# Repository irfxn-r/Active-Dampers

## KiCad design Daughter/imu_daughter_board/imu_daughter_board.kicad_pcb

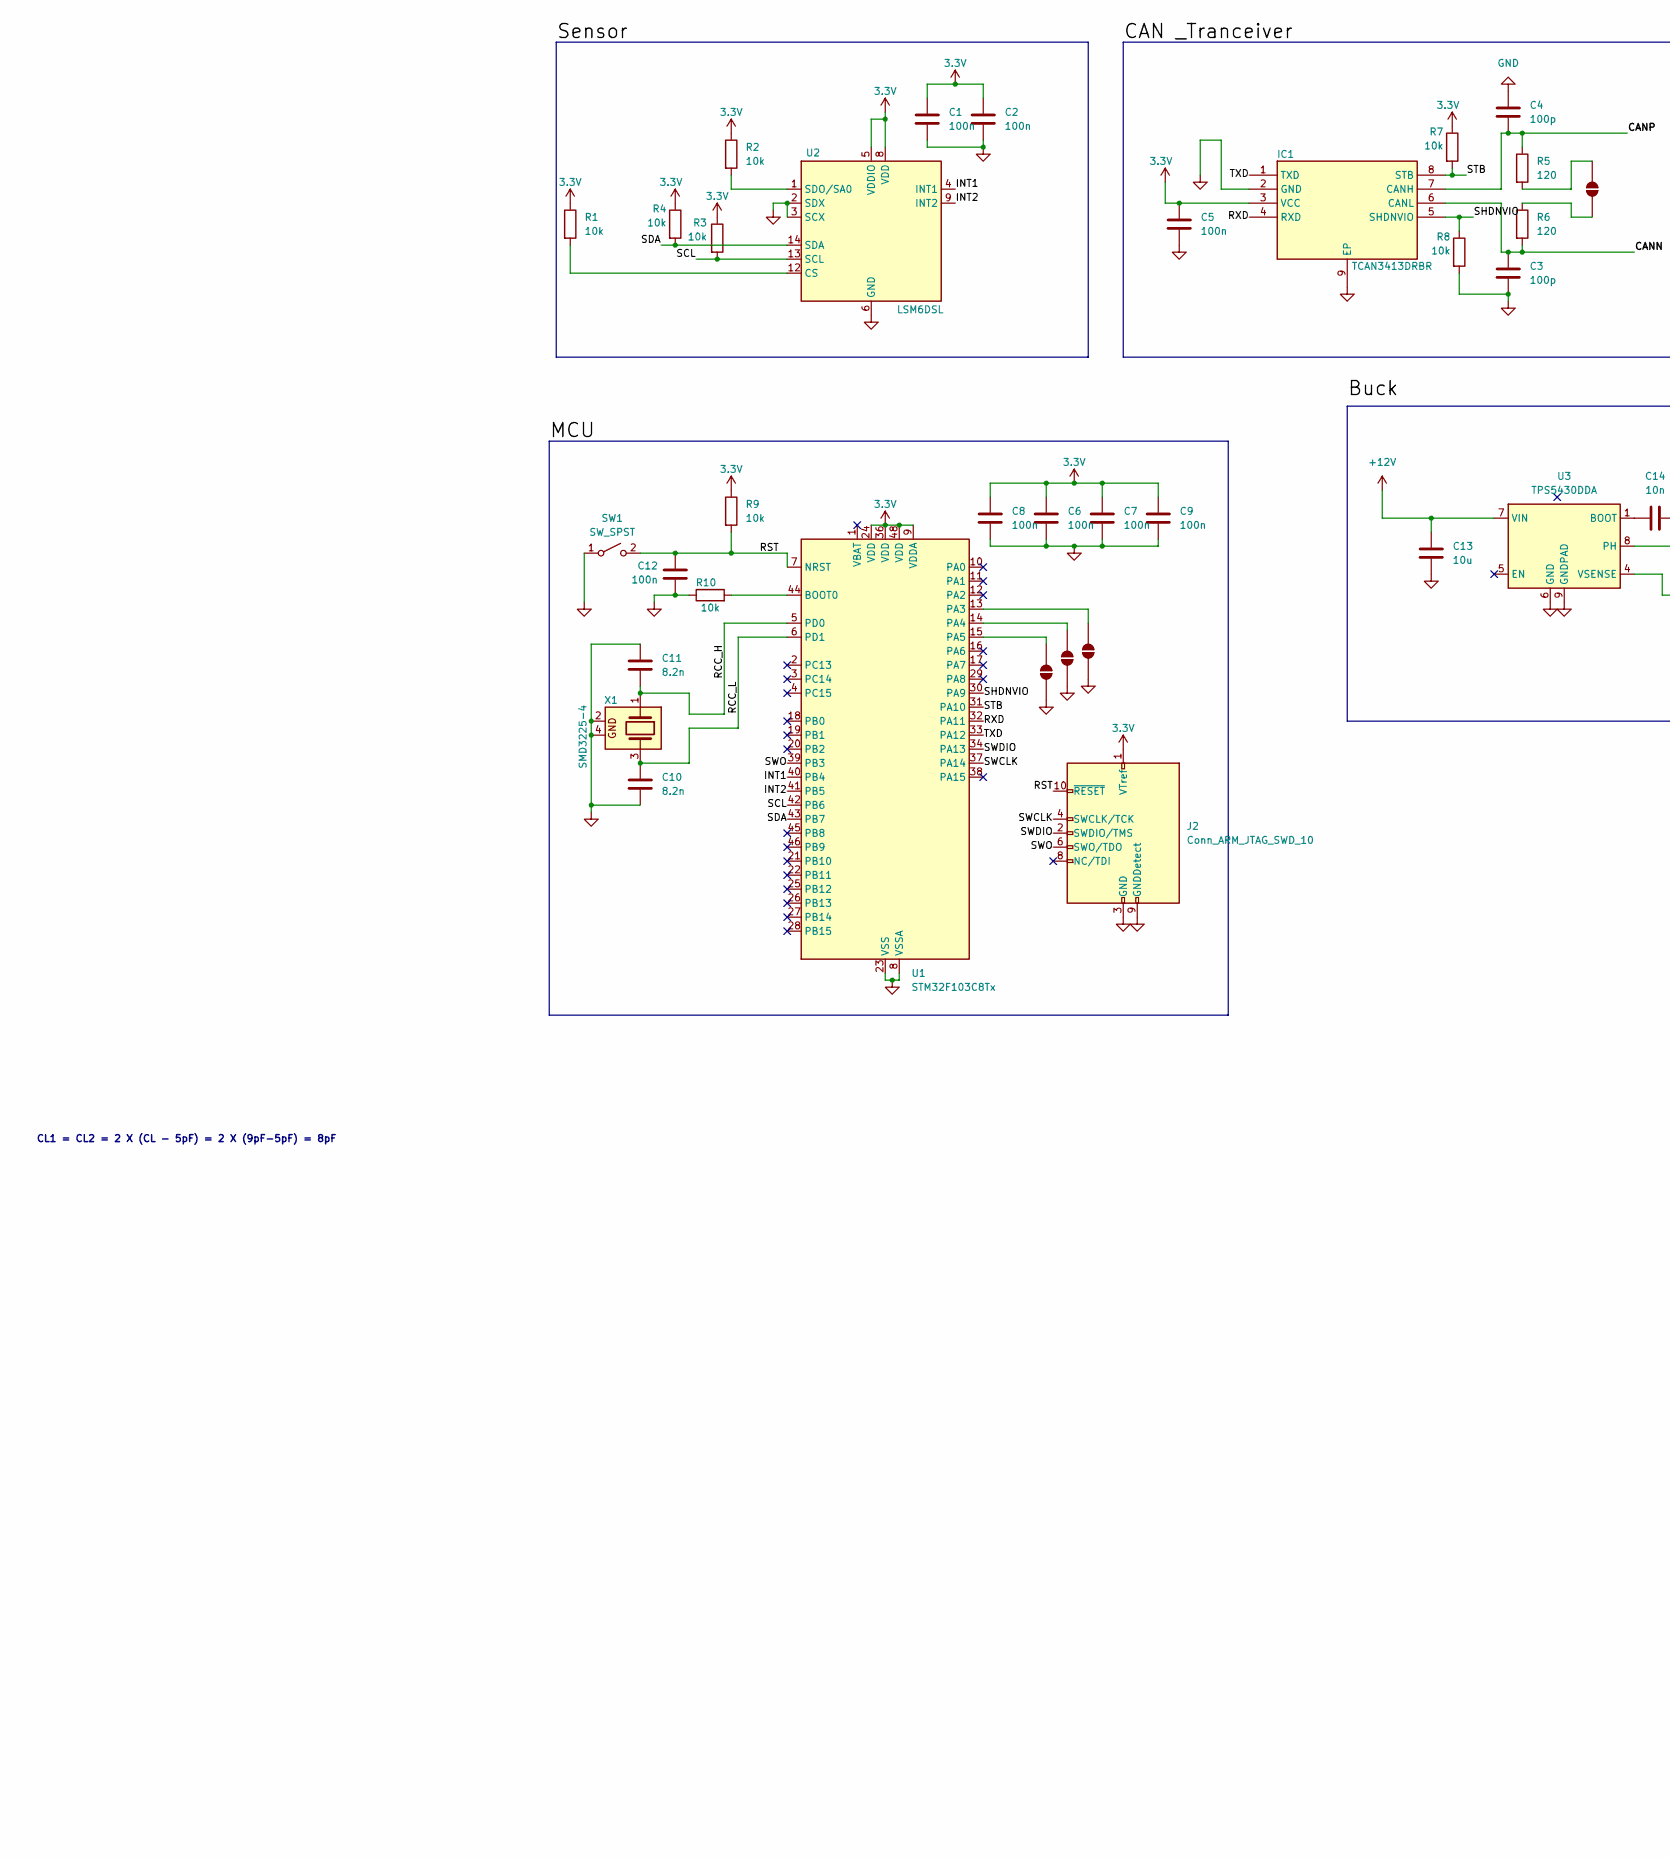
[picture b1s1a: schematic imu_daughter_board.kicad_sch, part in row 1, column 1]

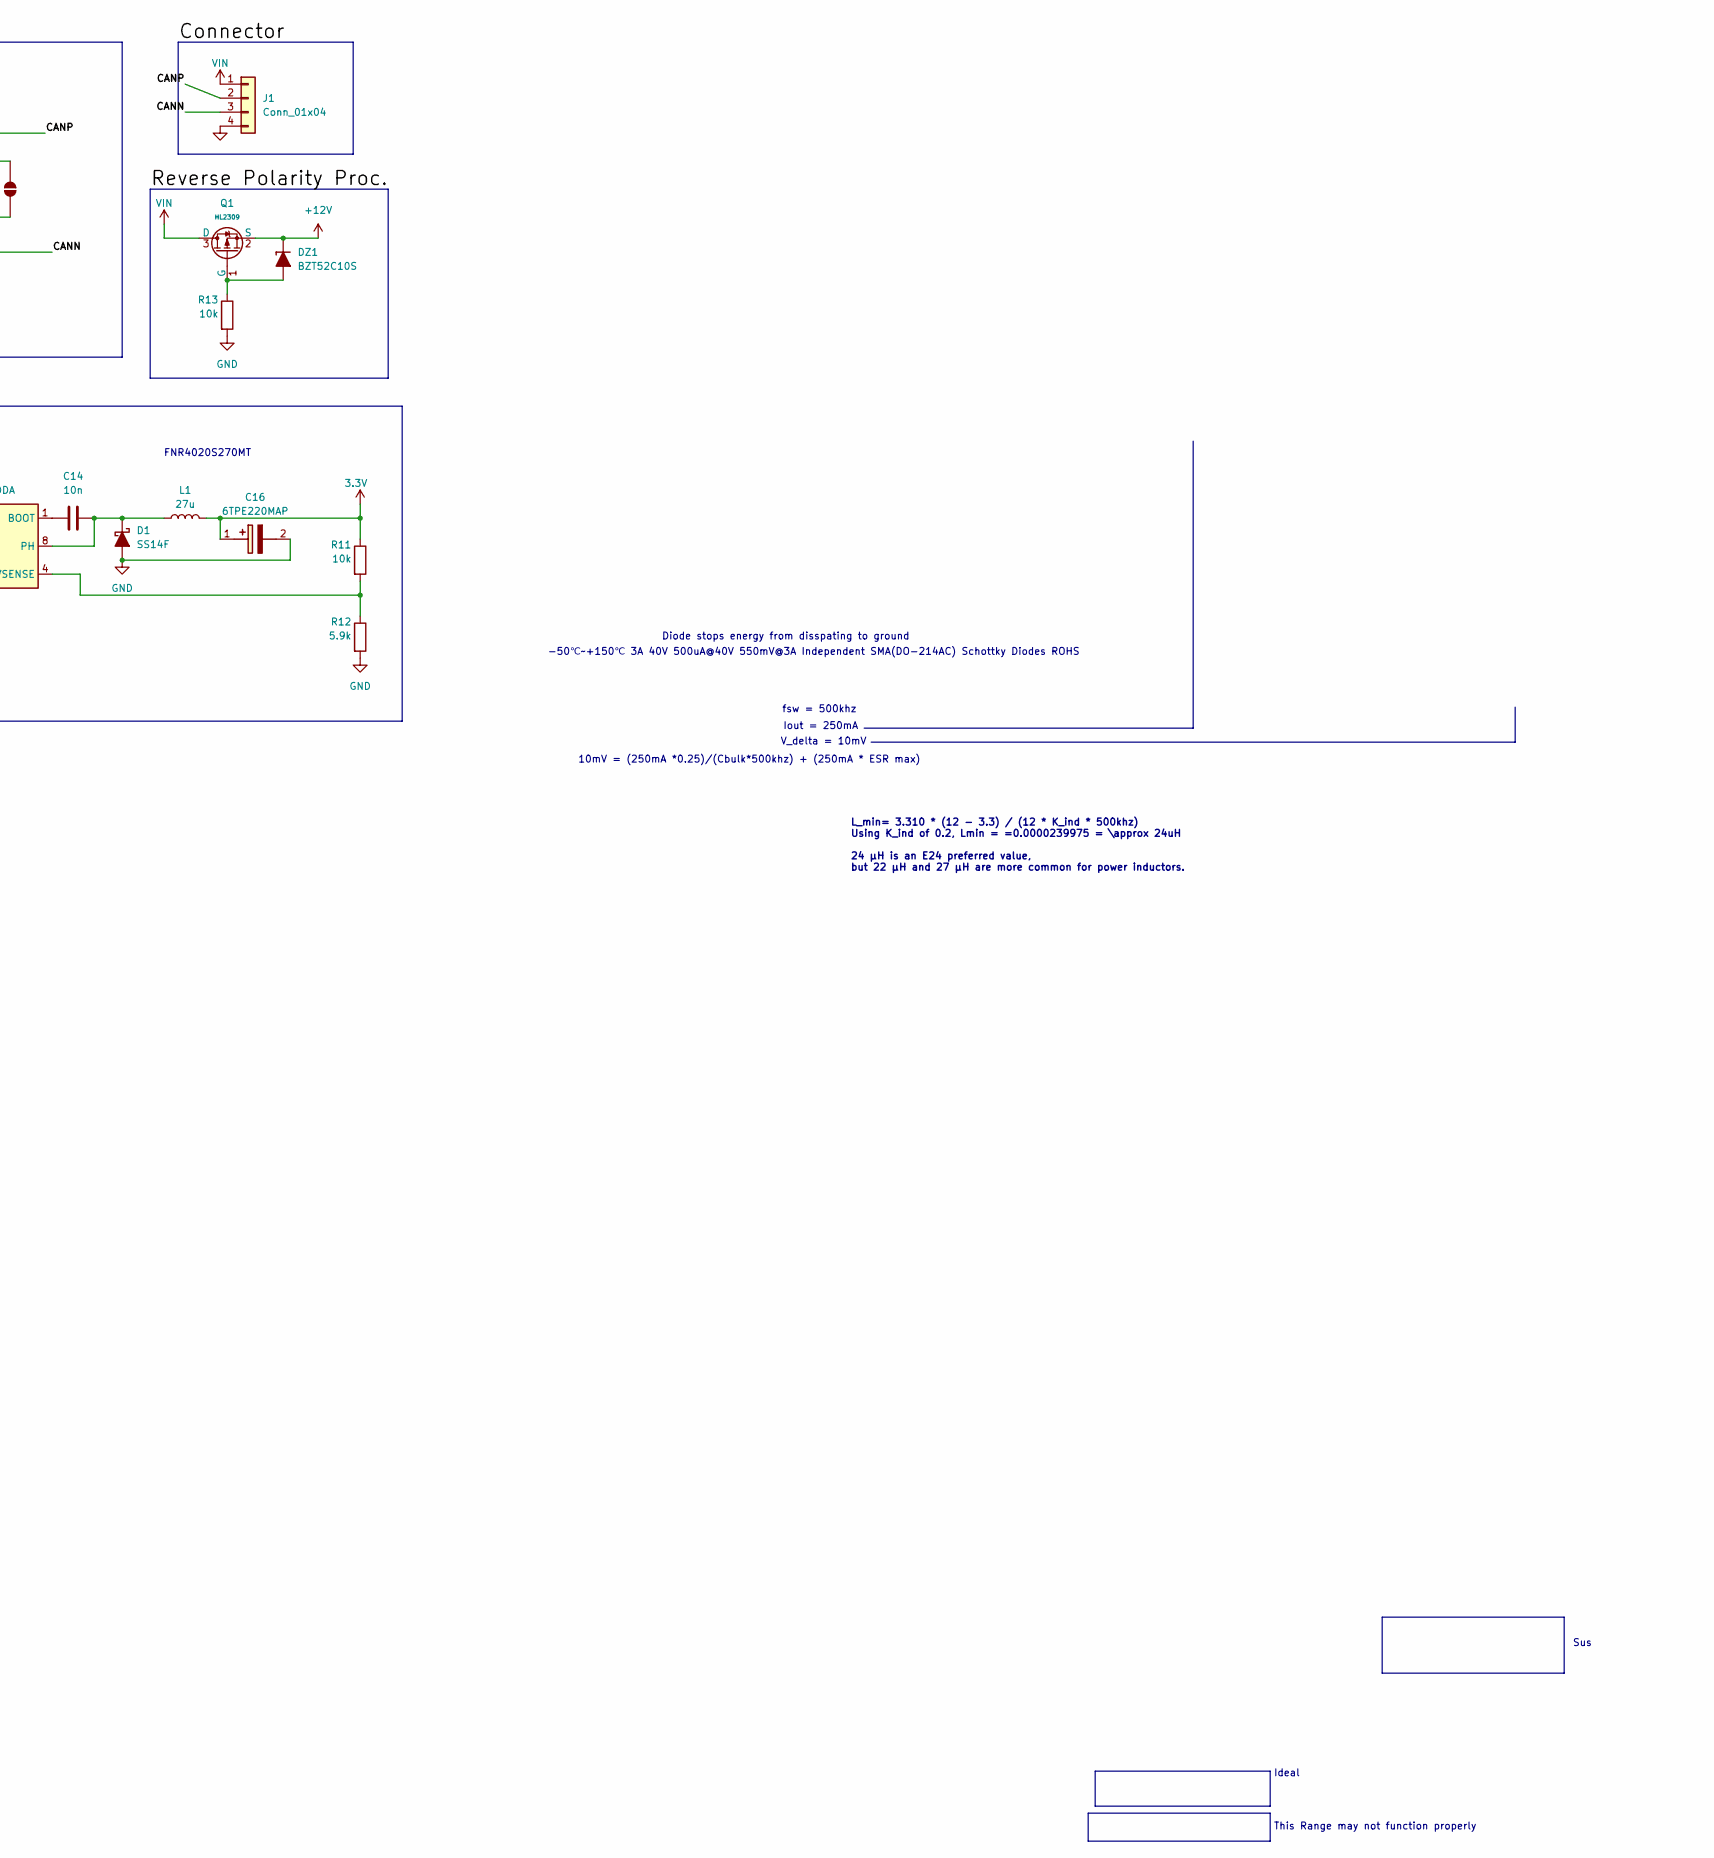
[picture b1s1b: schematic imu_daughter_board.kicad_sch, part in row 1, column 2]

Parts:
C1, C2, C5, C6, C7, C8, C9, C12: 100n; C_0402_1005Metric
C3, C4: 100p; C_0402_1005Metric
C10, C11: 8.2n; C_0402_1005Metric
C13: 10u; C_0603_1608Metric_Pad1.05x0.95mm
C14: 10n; C_0603_1608Metric_Pad1.05x0.95mm
C16: 6TPE220MAP; 2R5TAE330MF; Mouser Part Number 667-6TPE220MAP
D1: SS14F; D_SMAFL
DZ1: BZT52C10S; D_SOD-323
IC1: TCAN3413DRBR; SON65P300X300X100-9N-D; Mouser Part Number 595-TCAN3413DRBR
J1: Conn_01x04; SolderWire-0.5sqmm_1x04_P4.6mm_D0.9mm_OD2.1mm
J2: Conn_ARM_JTAG_SWD_10; SHF10501FDTH
JP1, JP2, JP3, JP4: SolderJumper_2_Open; SolderJumper-2_P1.3mm_Open_Pad1.0x1.5mm
L1: 27u; L_Taiyo-Yuden_MD-4040
Q1: HL2309; Q_SOT-23; Part HL2309; LCSC C28646263
R1, R2, R3, R4, R7, R8, R9, R10: 10k; C_0402_1005Metric
R5, R6: 120; R_0402_1005Metric
R11, R13: 10k; R_0603_1608Metric
R12: 5.9k; R_0603_1608Metric
SW1: SW_SPST; SW_SPST_TS-1088-xR025
U1: STM32F103C8Tx; LQFP-48_7x7mm_P0.5mm
U2: LSM6DSL; LGA-14_3x2.5mm_P0.5mm_LayoutBorder3x4y
U3: TPS5430DDA; TI_SO-PowerPAD-8_ThermalVias
X1: SMD3225-4; Crystal_SMD_3225-4Pin_3.2x2.5mm

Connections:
3.3V: C1.2, C2.1, C5.2, C6.2, C7.1, C8.2, C9.1, C16.1 (+), IC1.3 (VCC), J2.1 (VTref), L1.2, R1.1, R1.2, R2.1, R3.1, R4.1, R7.1, R9.1, R11.1, U1.9 (VDDA), U1.24 (VDD), U1.36 (VDD), U1.48 (VDD), U2.5 (VDDIO), U2.8 (VDD), U2.12 (CS)
+12V: C13.1, DZ1.1 (K), Q1.2 (S), U3.7 (VIN)
/CANN: C3.1, IC1.6 (CANL), J1.3, R6.2
/CANP: C4.2, IC1.7 (CANH), J1.2, R5.1
/INT1: U1.40 (PB4), U2.4 (INT1)
/INT2: U1.41 (PB5), U2.9 (INT2)
/RCC_H: C11.1, U1.5 (PD0), X1.1
/RCC_L: C10.2, U1.6 (PD1), X1.3
/RST: C12.2, J2.10 (~RESET), R9.2, SW1.2 (B), U1.7 (NRST)
/RXD: IC1.4 (RXD), U1.32 (PA11)
/SCL: R3.2, U1.42 (PB6), U2.13 (SCL)
/SDA: R4.2, U1.43 (PB7), U2.14 (SDA)
/SHDNVIO: IC1.5 (SHDNVIO), R8.1, U1.30 (PA9)
/STB: IC1.8 (STB), R7.2, U1.31 (PA10)
/SWCLK: J2.4 (SWCLK/TCK), U1.37 (PA14)
/SWDIO: J2.2 (SWDIO/TMS), U1.34 (PA13)
/SWO: J2.6 (SWO/TDO), U1.39 (PB3)
/TXD: IC1.1 (TXD), U1.33 (PA12)
GND: C1.1, C2.2, C3.2, C4.1, C5.1, C6.1, C7.2, C8.1, C9.2, C10.1, C11.2, C12.1, C13.2, C16.2 (-), D1.2 (A), IC1.2 (GND), IC1.9 (EP), J1.4, J2.3 (GND), J2.5 (GND), J2.9 (GNDDetect), JP2.1 (A), JP3.1 (A), JP4.1 (A), R8.2, R10.1, R12.2, R13.2, SW1.1 (A), U1.8 (VSSA), U1.23 (VSS), U1.35 (VSS), U1.47 (VSS), U2.2 (SDX), U2.3 (SCX), U2.6 (GND), U2.7 (GND), U3.6 (GND), U3.9 (GNDPAD), X1.2, X1.4
unnamed: C14.2, D1.1 (K), L1.1, U3.8 (PH)
unnamed: DZ1.2 (A), Q1.1 (G), R13.1
unnamed: JP1.1 (A), R6.1
unnamed: JP1.2 (B), R5.2
unnamed: JP2.2 (B), U1.15 (PA5)
unnamed: JP3.2 (B), U1.14 (PA4)
unnamed: JP4.2 (B), U1.13 (PA3)
unnamed: R10.2, U1.44 (BOOT0)
unnamed: R2.2, U2.1 (SDO/SA0)
unnamed: C14.1, U3.1 (BOOT)
unnamed: R11.2, R12.1, U3.4 (VSENSE)
VIN: J1.1, Q1.3 (D)

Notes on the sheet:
-50℃~+150℃ 3A 40V 500uA@40V 550mV@3A Independent SMA(DO-214AC) Schottky Diodes ROHS
This Range may not function properly
Sus
10mV = (250mA *0.25)/(Cbulk*500khz) + (250mA * ESR max)
CL1 = CL2 = 2 X (CL - 5pF) = 2 X (9pF-5pF) = 8pF
V_delta = 10mV
Ideal
Vpp max = 20mV
R2 = R1 * 1.221 / (3.3 - 1.221) R1 = 10kohm R2 = 10e3 * 1.221 / (3.3 - 1.221) 5873.01587302
Maybe not important yet
L_min= 3.310 * (12 - 3.3) / (12 * K_ind * 500khz) Using K_ind of 0.2, Lmin = =0.0000239975 = \approx 24uH 24 µH is an E24 preferred value, but 22 µH and 27 µH are more common for power inductors.
Use 5.90 kΩ, 1%-it's a standard E96 value closest to your calculated 5.873 kΩ.
fsw = 500khz
FNR4020S270MT
Diode stops energy from disspating to ground
Iout = 250mA

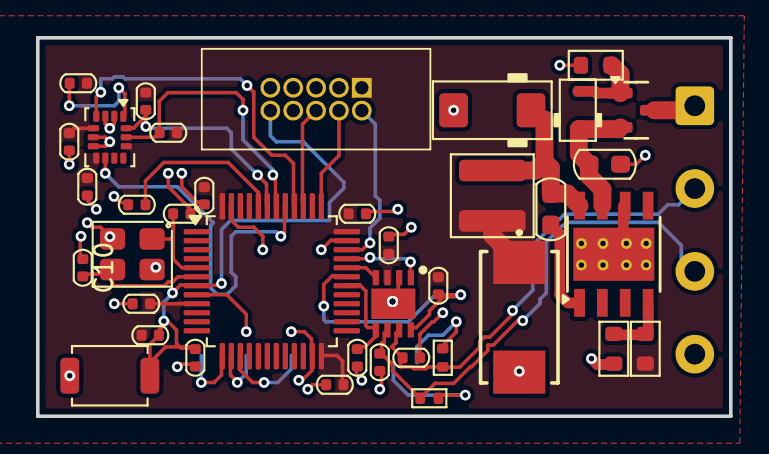
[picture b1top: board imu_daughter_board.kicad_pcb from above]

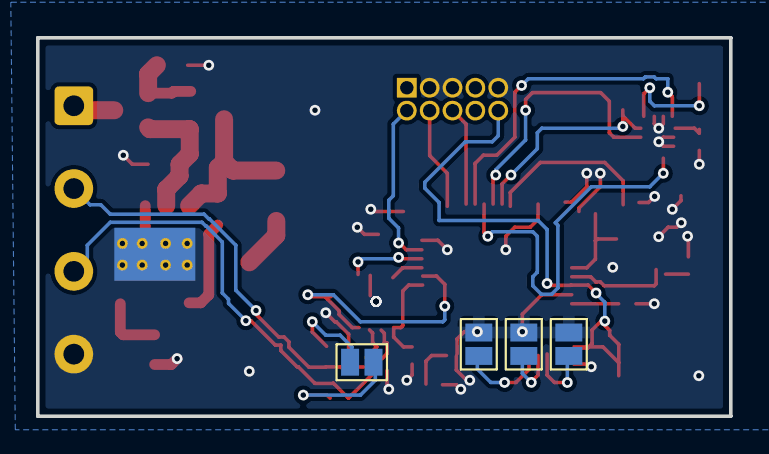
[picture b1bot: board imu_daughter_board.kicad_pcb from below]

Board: 2 copper layers, 38.5 x 21.0 mm, 43 parts (4 on the bottom side), 31 nets.

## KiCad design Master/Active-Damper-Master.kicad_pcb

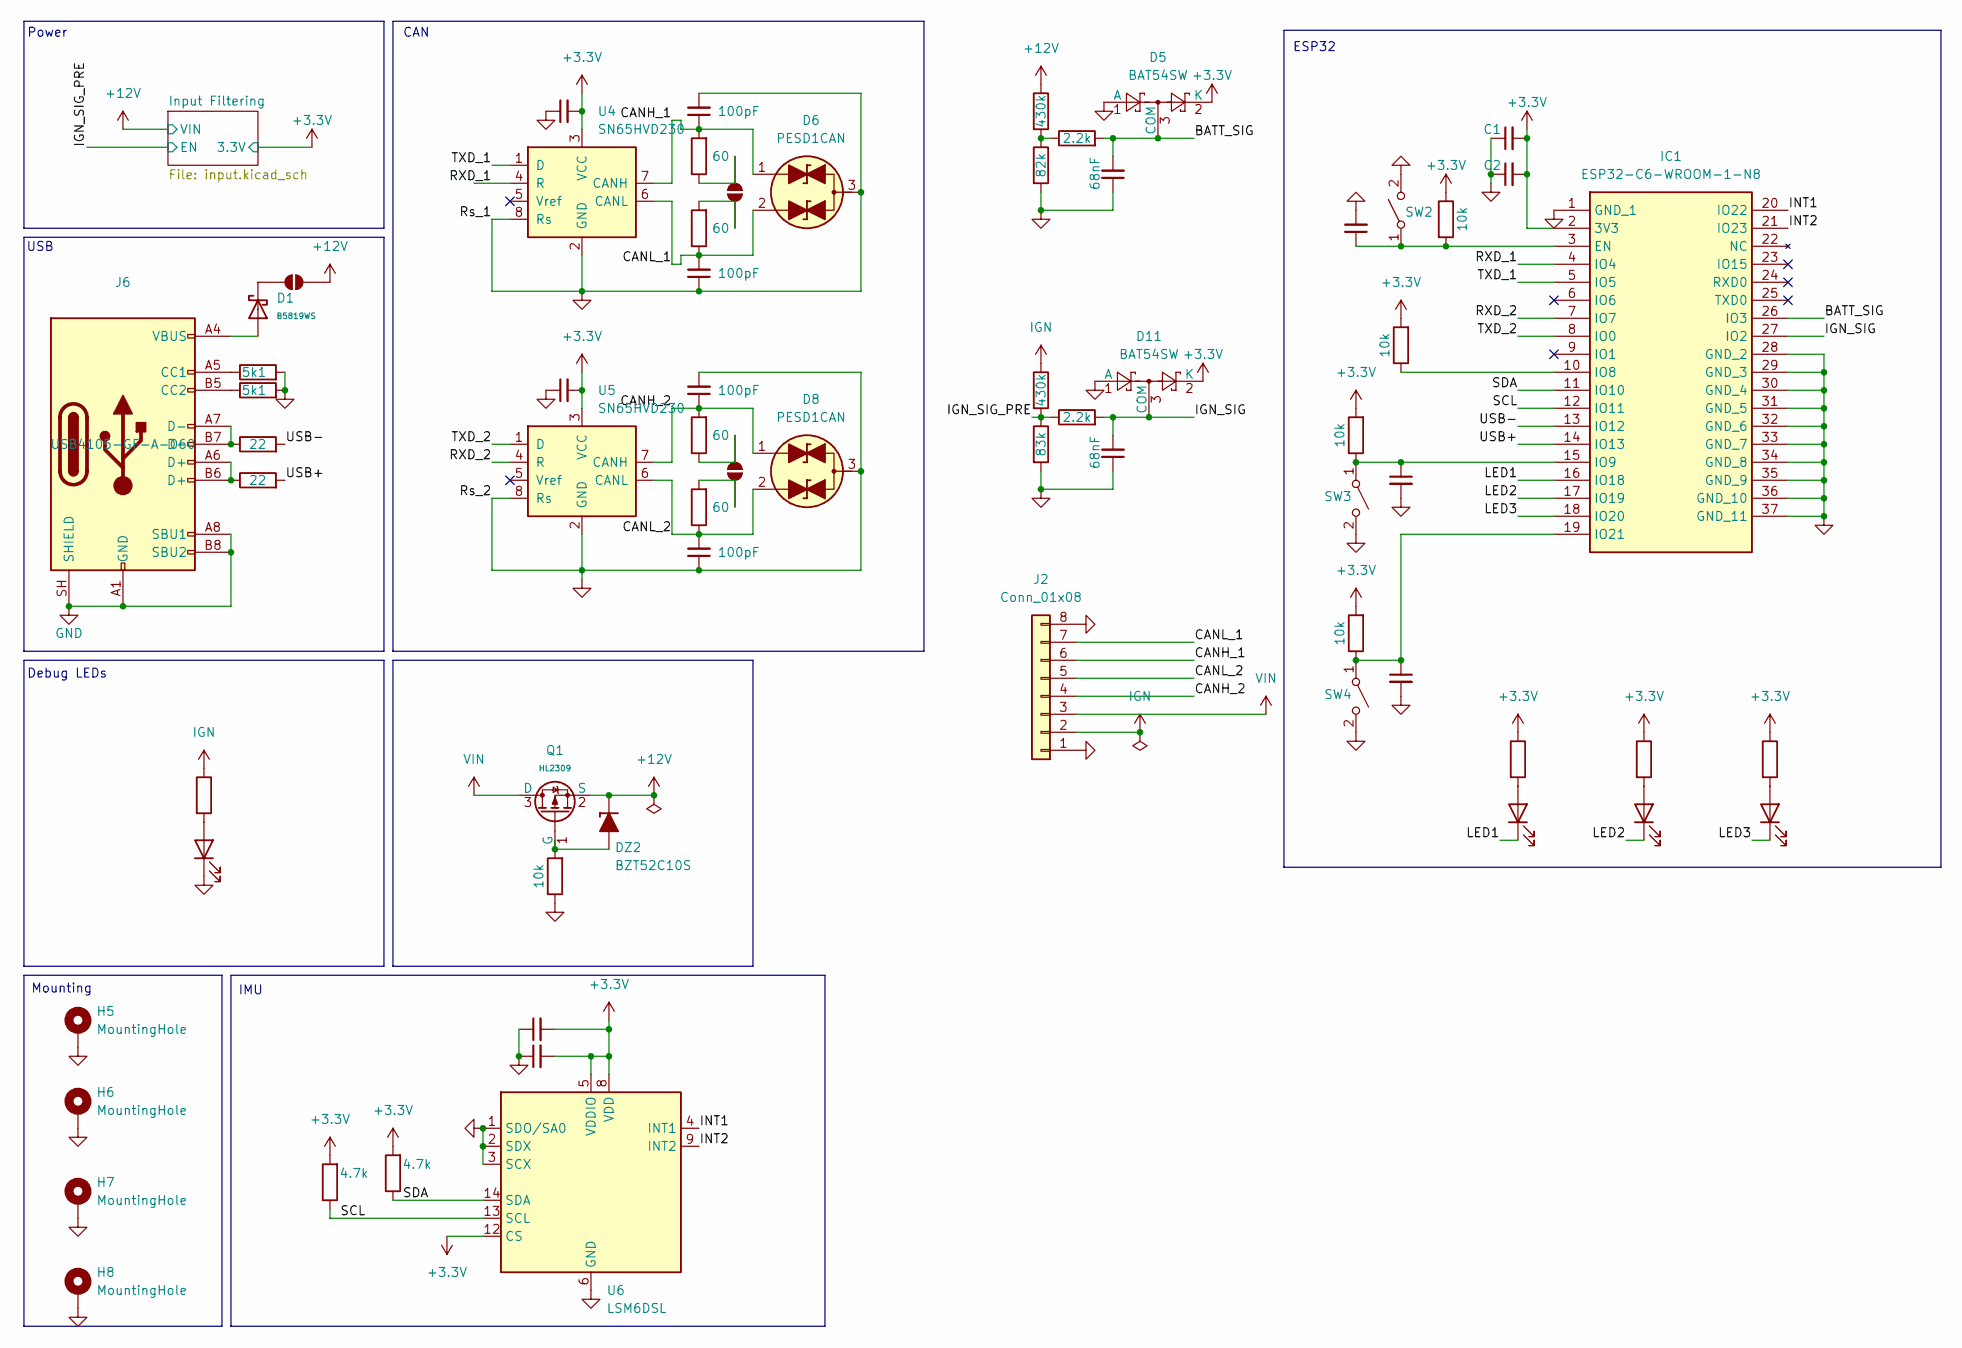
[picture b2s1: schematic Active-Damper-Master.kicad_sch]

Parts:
C1, C24, C25: 1uF; C_0603_1608Metric; Manufacturer_Part_Number TMK105BJ105MV-F; LCSC C15849
C2, C21, C26: 10uF; C_0603_1608Metric; Manufacturer_Part_Number CL05A106MP5NUNC; LCSC C96446
C19, C20: 100nF; C_0603_1608Metric; Manufacturer_Part_Number TMK105BJ105MV-F; LCSC C15849
C22: 1uF; C_0603_1608Metric; Manufacturer_Part_Number CL05A106MP5NUNC; LCSC C96446
C48, C49: 68nF; C_0603_1608Metric; Manufacturer_Part_Number CC0402KRX7R9BB683; LCSC C31658
C54, C56, C57, C58: 100pF; C_0603_1608Metric; LCSC C14858
D1: B5819WS; D_SOD-323; Forward Voltage (Vf@If) 900mV@3A; Reverse Voltage (Vr) 40V; Part B5819WS; LCSC C64886
D5, D11: BAT54SW; SOT-323_SC-70
D6, D8: PESD1CAN; SOT-23; LCSC C15771
D7, D9, D10, D12: LED BLUE; LED_0603_1608Metric; Manufacturer_Part_Number VLMB1500-GS08; LCSC C2286
DZ2: BZT52C10S; D_SOD-323
H5, H6, H7, H8: MountingHole; MountingHole_3.2mm_M3_ISO14580_Pad_TopBottom
IC1: ESP32-C6-WROOM-1-N8; ESP32C6WROOM1N8; Mouser Part Number 356-ESP32C6WROOM1N8
J2: Conn_01x08; JST_VH_B8P-VH-B_1x08_P3.96mm_Vertical
J6: USB_C_Receptacle_USB2.0_16P; USB_C_Receptacle_HRO_TYPE-C-31-M-12; Manufacturer_Part_Number USB4105-GF-A-060; LCSC C165948
JP2, JP4: SolderJumper_2_Open; SolderJumper-2_P1.3mm_Open_RoundedPad1.0x1.5mm
JP3: SolderJumper_2_Open; SolderJumper-2_P1.3mm_Open_Pad1.0x1.5mm
Q1: HL2309; SOT-23; Part HL2309; LCSC C28646263
R3, R13: 430k; C_0603_1608Metric; Manufacturer_Part_Number RC0402FR-07150KL; LCSC C25803
R6, R7: 5k1; R_0603_1608Metric; Manufacturer_Part_Number RC0402FR-071KL; LCSC C23186
R8: 82k; C_0603_1608Metric; Manufacturer_Part_Number AC0402JR-7D10KL; LCSC C22967
R9: 4..7k; R_0603_1608Metric; Manufacturer_Part_Number CR0402-FX-5101GLF; LCSC C22975
R12, R15: 2.2k; C_0603_1608Metric; Manufacturer_Part_Number RC0402FR-072K2L; LCSC C4190
R14: 83k; C_0603_1608Metric; Manufacturer_Part_Number AC0402JR-7D10KL; LCSC C22967
R16, R17, R18: 1k; R_0603_1608Metric; Manufacturer_Part_Number CR0402-FX-5101GLF; LCSC C22975
R19, R20: 22; R_0402_1005Metric; Manufacturer_Part_Number RC0402FR-071KL; LCSC C23186
R23, R38, R39, R40, R41: 10k; R_0603_1608Metric; Manufacturer_Part_Number RC0402FR-071KL; LCSC C21190
R46, R47, R48, R49: 60; C_0603_1608Metric; LCSC C25196
R51, R54: 4.7k; R_0603_1608Metric; LCSC C23162
SW2, SW3, SW4: SW_SPST; SW_SPST_TS-1088-xR025; LCSC C720477
U4, U5: SN65HVD230; SOIC-8_3.9x4.9mm_P1.27mm
U6: LSM6DSL; LGA-14_3x2.5mm_P0.5mm_LayoutBorder3x4y

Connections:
+3.3V: C1.2, C2.2, C19.2, C20.2, C24.2, C25.2, D5.2 (K), D11.2 (K), IC1.2 (3V3), R16.1, R17.1, R18.1, R23.1, R38.2, R40.2, R41.2, R51.2, R54.2, U4.3 (VCC), U5.3 (VCC), U6.5 (VDDIO), U6.8 (VDD), U6.12 (CS)
+12V: DZ2.1 (K), JP3.2 (B), Q1.2 (S), R3.1; also elsewhere on the board
/BATT_SIG: C48.2, D5.3 (COM), IC1.26 (IO3), R12.2
/CANH_1: C56.1, D6.1 (A1), J2.6, R46.2, U4.7 (CANH)
/CANH_2: C57.1, D8.1 (A1), J2.4, R48.2, U5.7 (CANH)
/CANL_1: C54.2, D6.2 (A2), J2.7, R47.1, U4.6 (CANL)
/CANL_2: C58.2, D8.2 (A2), J2.5, R49.1, U5.6 (CANL)
/IGN_SIG: C49.2, D11.3 (COM), IC1.27 (IO2), R15.2
/IGN_SIG_PRE: R13.2, R14.1, R15.1; also elsewhere on the board
/INT1: IC1.20 (IO22), U6.4 (INT1)
/INT2: IC1.21 (IO23), U6.9 (INT2)
/LED1: D9.1 (K), IC1.16 (IO18)
/LED2: D10.1 (K), IC1.17 (IO19)
/LED3: D12.1 (K), IC1.18 (IO20)
/RXD_1: IC1.4 (IO4), U4.4 (R)
/RXD_2: IC1.7 (IO7), U5.4 (R)
/SCL: IC1.12 (IO11), R54.1, U6.13 (SCL)
/SDA: IC1.11 (IO10), R51.1, U6.14 (SDA)
/TXD_1: IC1.5 (IO5), U4.1 (D)
/TXD_2: IC1.8 (IO0), U5.1 (D)
/USB+: IC1.14 (IO13), R20.2
/USB-: IC1.13 (IO12), R19.2
GND: C1.1, C2.1, C19.1, C20.1, C21.2, C22.2, C24.1, C25.1, C26.2, C48.1, C49.1, C54.1, C56.2, C57.2, C58.1, D5.1 (A), D6.3 (Com), D7.1 (K), D8.3 (Com), D11.1 (A), H5.1 (1_1), H6.1 (1_1), H7.1 (1_1), H8.1 (1_1), IC1.1 (GND_1), IC1.28 (GND_2), IC1.29 (GND_3), IC1.30 (GND_4), IC1.31 (GND_5), IC1.32 (GND_6), IC1.33 (GND_7), IC1.34 (GND_8), IC1.35 (GND_9), IC1.36 (GND_10), IC1.37 (GND_11), J2.1, J2.8, J6.A1 (GND), J6.A8 (SBU1), J6.A12 (GND), J6.B1 (GND), J6.B8 (SBU2), J6.B12 (GND), J6.SH (SHIELD), R6.2, R7.2, R8.2, R14.2, R39.1, SW2.2 (B), SW3.2 (B), SW4.2 (B), U4.2 (GND), U4.8 (Rs), U5.2 (GND), U5.8 (Rs), U6.1 (SDO/SA0), U6.2 (SDX), U6.3 (SCX), U6.6 (GND), U6.7 (GND); also elsewhere on the board
IGN: J2.2, R9.1, R13.1
unnamed: D1.2, J6.A4 (VBUS), J6.A9 (VBUS), J6.B4 (VBUS), J6.B9 (VBUS)
unnamed: D7.2 (A), R9.2
unnamed: D9.2 (A), R16.2
unnamed: D10.2 (A), R17.2
unnamed: D12.2 (A), R18.2
unnamed: DZ2.2 (A), Q1.1 (G), R39.2
unnamed: C22.1, IC1.3 (EN), R23.2, SW2.1 (A)
unnamed: IC1.10 (IO8), R41.1
unnamed: C21.1, IC1.15 (IO9), R38.1, SW3.1 (A)
unnamed: C26.1, IC1.19 (IO21), R40.1, SW4.1 (A)
unnamed: J6.A5 (CC1), R6.1
unnamed: J6.B5 (CC2), R7.1
unnamed: J6.A6 (D+), J6.B6 (D+), R20.1
unnamed: J6.A7 (D-), J6.B7 (D-), R19.1
unnamed: JP2.1 (A), R49.2
unnamed: JP2.2 (B), R48.1
unnamed: D1.1, JP3.1 (A)
unnamed: JP4.1 (A), R47.2
unnamed: JP4.2 (B), R46.1
unnamed: R3.2, R8.1, R12.1
VIN: J2.3, Q1.3 (D)

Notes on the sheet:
ESP32
IMU
CAN
Power
USB
Debug LEDs
Mounting

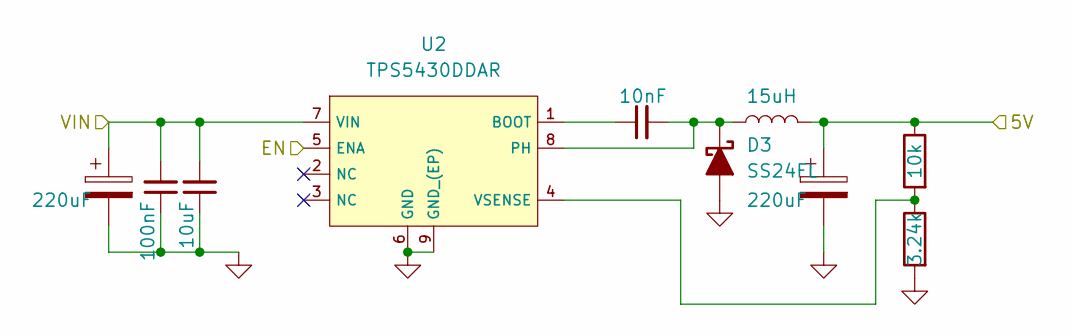
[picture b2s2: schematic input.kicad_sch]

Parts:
C3, C10: 220uF; CP_Radial_D8.0mm_P3.50mm
C9: 10nF; C_0603_1608Metric; Manufacturer_Part_Number GRM155R60J226ME11D; LCSC C57112
C34: 100nF; C_0603_1608Metric; Manufacturer_Part_Number CL05A106MP5NUNC; LCSC C21122
C35: 10uF; C_0603_1608Metric; Manufacturer_Part_Number CL05A106MP5NUNC; LCSC C21122
D3: SS24FL; D_SOD-123F
L1: 15uH; L_Taiyo-Yuden_NR-40xx; Manufacturer_Part_Number SLO0630H150MTT; LCSC C2045384
R21: 10k; R_0603_1608Metric; Manufacturer_Part_Number RC0402FR-0710KL; LCSC C25804
R22: 3.24k; R_0603_1608Metric; Manufacturer_Part_Number RC0402FR-0710KL; LCSC C22978
U2: TPS5430DDAR; ESOP-8_L4.9-W3.9-P1.27-LS6.0-TL-EP; Output Voltage 1.221V~32.04V; Input Voltage 5.5V~36V; Part TPS5430DDAR; LCSC C9864

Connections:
+12V: C3.1, C34.2, C35.2, U2.7 (VIN); also elsewhere on the board
/IGN_SIG_PRE: U2.5 (ENA); also elsewhere on the board
/Input Filtering/5V: C10.1, L1.2, R21.2
GND: C3.2, C10.2, C34.1, C35.1, D3.2 (A), R22.1, U2.6 (GND), U2.9 (GND_(EP)); also elsewhere on the board
unnamed: C9.2, D3.1 (K), L1.1, U2.8 (PH)
unnamed: C9.1, U2.1 (BOOT)
unnamed: R21.1, R22.2, U2.4 (VSENSE)

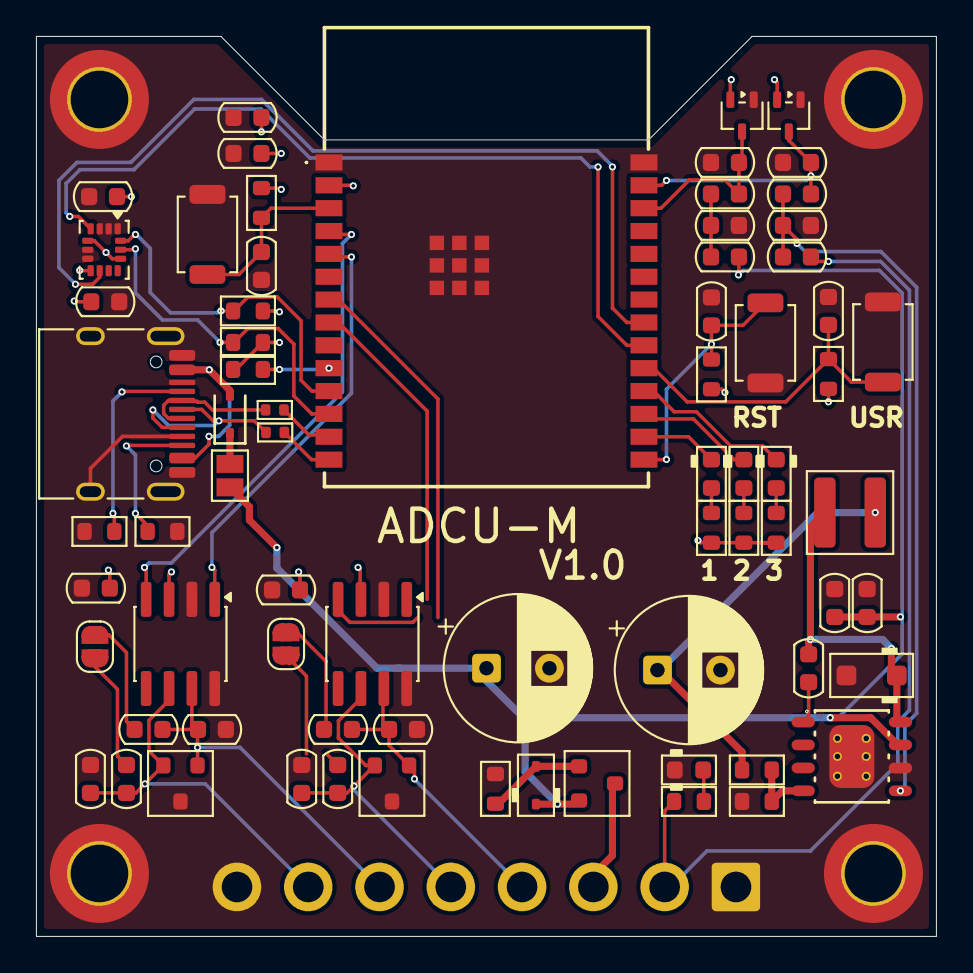
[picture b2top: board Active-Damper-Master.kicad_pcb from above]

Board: 2 copper layers, 50.0 x 50.0 mm, 77 parts (1 on the bottom side), 49 nets.

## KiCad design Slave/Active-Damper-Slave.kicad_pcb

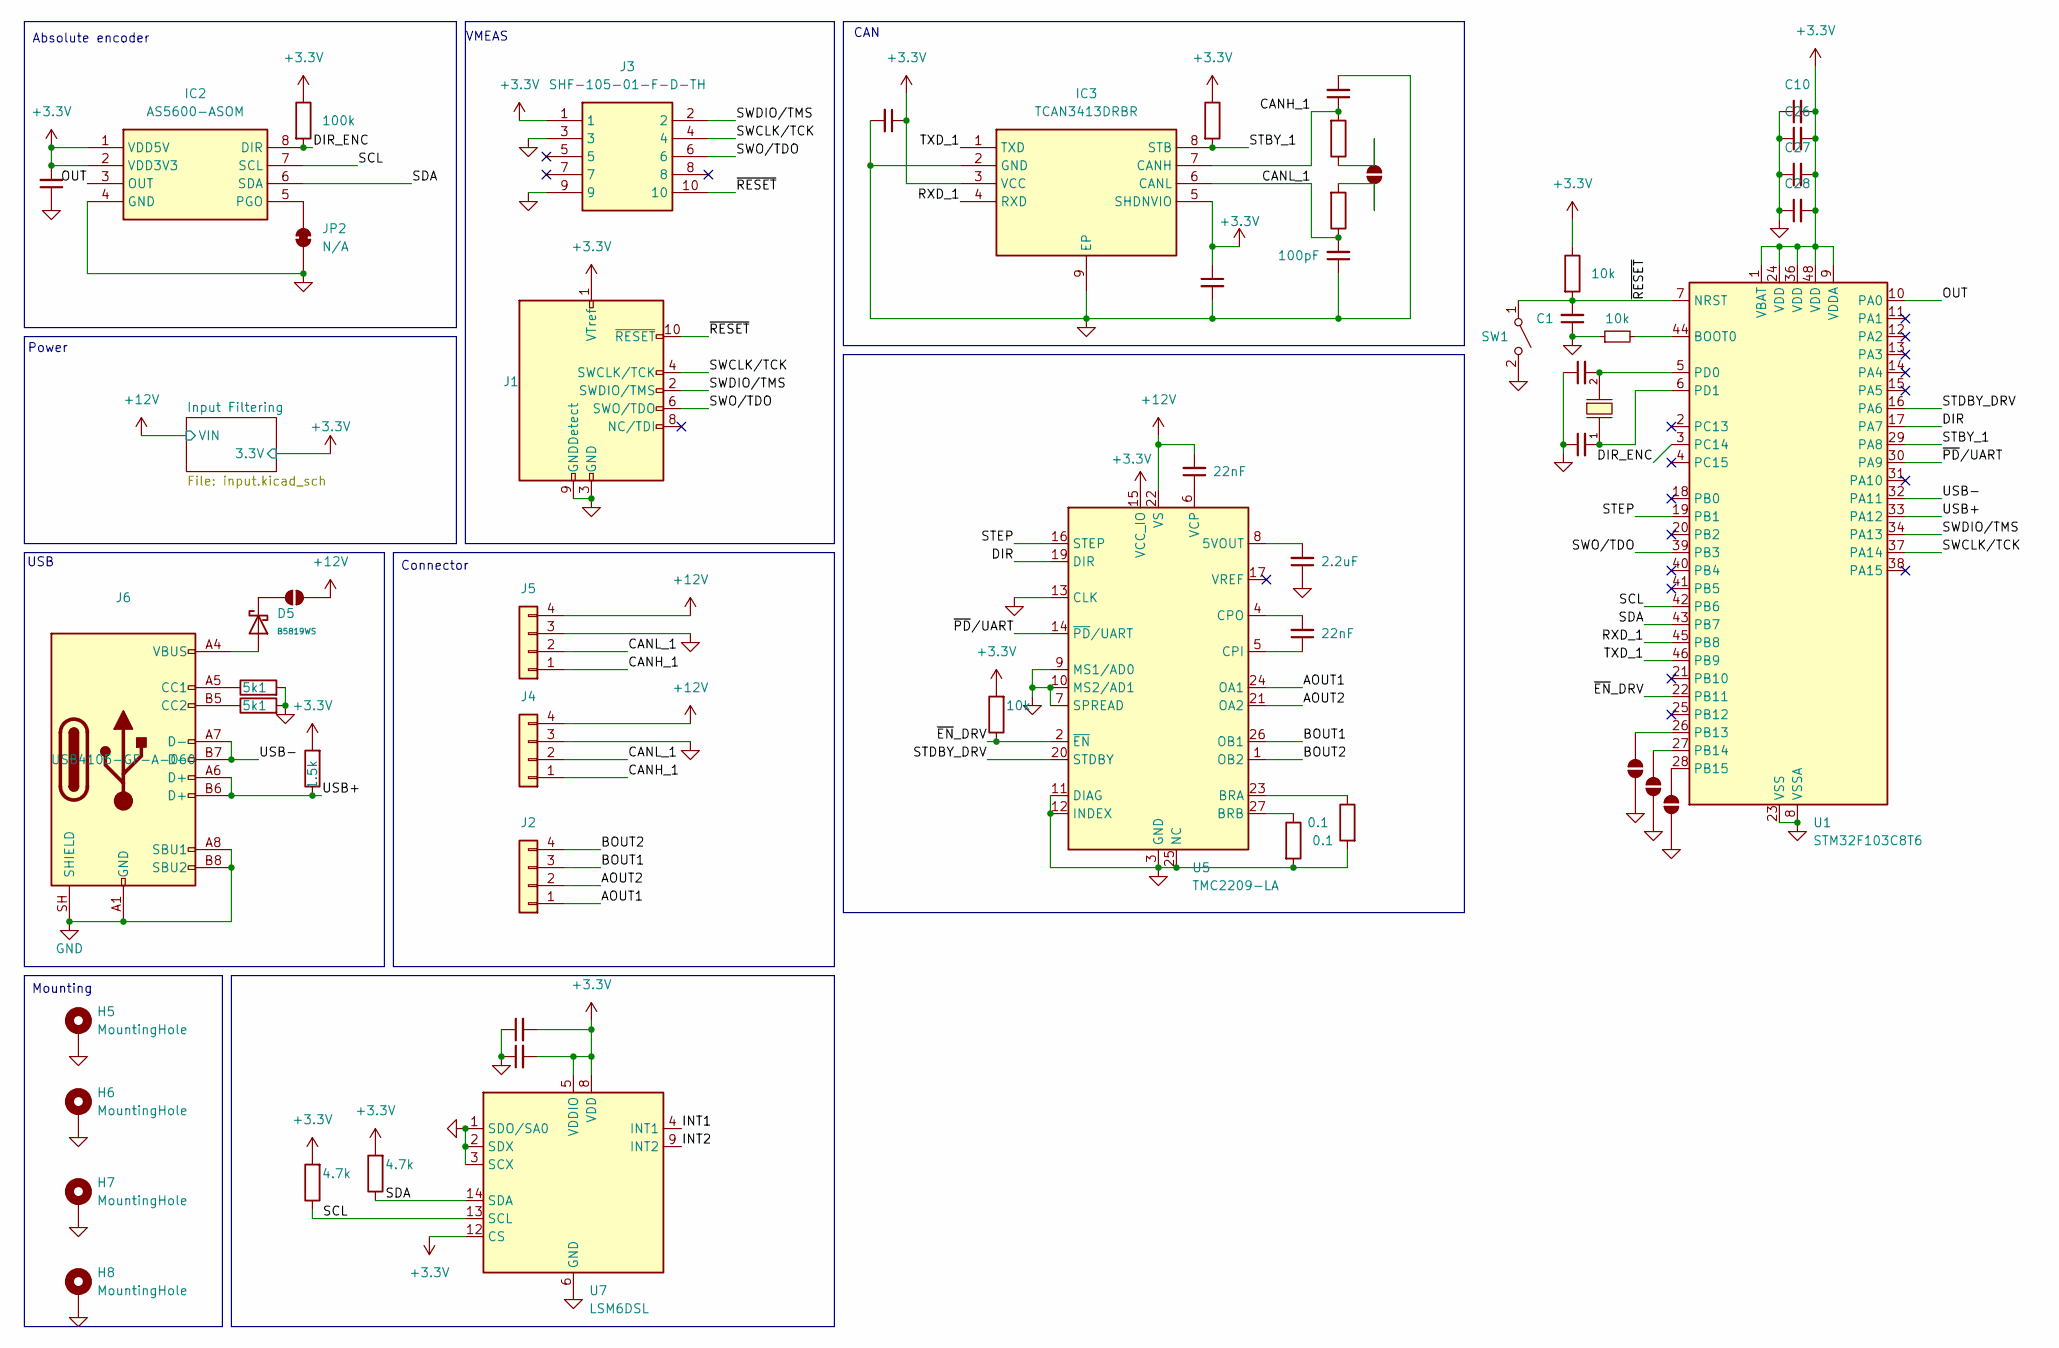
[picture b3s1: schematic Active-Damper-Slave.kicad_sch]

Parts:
C1, C26: 100nF; C_0402_1005Metric; Manufacturer_Part_Number MCASU105SB5104MFNA01; LCSC C14663
C2, C29: 22pF; C_0402_1005Metric; Manufacturer_Part_Number MCASU105SB5104MFNA01; LCSC C1653
C10, C28: 10uF; C_0402_1005Metric; Manufacturer_Part_Number CL05A106MP5NUNC; LCSC C96446
C20, C24, C25, C27: 1uF; C_0402_1005Metric; Manufacturer_Part_Number TMK105BJ105MV-F; LCSC C15849
C22, C30: 22nF; C_0603_1608Metric; Manufacturer_Part_Number CL05A106MP5NUNC; LCSC C23630
C31: 2.2uF; C_0402_1005Metric; Manufacturer_Part_Number CL05A106MP5NUNC; LCSC C23630
C39, C40: 100nF; C_0402_1005Metric; Manufacturer_Part_Number TMK105BJ105MV-F; LCSC C15849
C59, C60: 100pF; C_0402_1005Metric; LCSC C14858
D5: B5819WS; D_SOD-323; Forward Voltage (Vf@If) 900mV@3A; Reverse Voltage (Vr) 40V; Part B5819WS; LCSC C64886
H5, H6, H7, H8: MountingHole; MountingHole_3.2mm_M3_ISO14580_Pad_TopBottom
IC2: AS5600-ASOM; SOIC127P600X175-8N; Mouser Part Number 985-AS5600-ASOM
IC3: TCAN3413DRBR; SON65P300X300X100-9N-D; Mouser Part Number 595-TCAN3413DRBR
J1: Conn_ARM_JTAG_SWD_10; SHF10501FDTH
J2, J4, J5: FL; SolderWire-0.5sqmm_1x04_P4.6mm_D0.9mm_OD2.1mm
J3: SHF-105-01-F-D-TH; SHF10501FDTH; Mouser Part Number 200-SHF10501FDTH
J6: USB_C_Receptacle_USB2.0_16P; USB_C_Receptacle_HRO_TYPE-C-31-M-12; Manufacturer_Part_Number USB4105-GF-A-060; LCSC C165948
JP1, JP5, JP6: SolderJumper_2_Open; SolderJumper-2_P1.3mm_Open_RoundedPad1.0x1.5mm
JP2: SolderJumper_2_Bridged; SolderJumper-2_P1.3mm_Bridged_Pad1.0x1.5mm; Manufacturer_Part_Number N/A
JP3, JP4: SolderJumper_2_Open; SolderJumper-2_P1.3mm_Open_Pad1.0x1.5mm
R1: 10k; R_0402_1005Metric; Manufacturer_Part_Number RC0402FR-071KL; LCSC C21190
R2: 10k; R_0402_1005Metric; Manufacturer_Part_Number AC0402FR-7D100KL; LCSC C25804
R4, R5: 0.1; R_2010_5025Metric; Manufacturer_Part_Number RC0402FR-071KL; LCSC C21190
R6, R7: 5k1; R_0603_1608Metric; Manufacturer_Part_Number RC0402FR-071KL; LCSC C23186
R10, R12: 100k; R_0402_1005Metric; Manufacturer_Part_Number RC0402FR-071KL; LCSC C21190
R11: 1.5k; R_0603_1608Metric; Manufacturer_Part_Number RC0402FR-071KL; LCSC C23186
R52, R55: 60; C_0603_1608Metric; LCSC C25196
R56, R57: 4.7k; R_0402_1005Metric; LCSC C23162
R58: 10k; R_0402_1005Metric; LCSC C23162
SW1: SW_SPST; SW_SPST_TS-1088-xR025; LCSC C720477
U1: STM32F103C8T6; LQFP-48_7x7mm_P0.5mm; Operating Voltage Range 2V~3.6V; Low Voltage Detection T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 2V~3.6V; Part STM32F103C8T6; LCSC C8734
U5: TMC2209-LA; VQFN-28-1EP_5x5mm_P0.5mm_EP3.7x3.7mm_ThermalVias; LCSC C2150710
U7: LSM6DSL; LGA-14_3x2.5mm_P0.5mm_LayoutBorder3x4y
ye1: X50328MSB2GI; CRYSTAL-SMD_L5.0-W3.2; Frequency Tolerance ±10ppm; Part X50328MSB2GI; LCSC C115962

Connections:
+3.3V: C10.2, C20.2, C24.1, C25.1, C26.2, C27.2, C28.2, C39.2, C40.2, IC2.1 (VDD5V), IC2.2 (VDD3V3), IC3.3 (VCC), IC3.5 (SHDNVIO), J1.1 (VTref), J3.1, R1.1, R10.1, R11.2, R12.1, R56.2, R57.2, R58.2, U1.1 (VBAT), U1.9 (VDDA), U1.24 (VDD), U1.36 (VDD), U1.48 (VDD), U5.15 (VCC_IO), U7.5 (VDDIO), U7.8 (VDD), U7.12 (CS); also elsewhere on the board
+12V: C30.2, J4.4, J5.4, JP3.2 (B), U5.22 (VS), U5.28 (VS); also elsewhere on the board
/AOUT1: J2.1, U5.24 (OA1)
/AOUT2: J2.2, U5.21 (OA2)
/BOUT1: J2.3, U5.26 (OB1)
/BOUT2: J2.4, U5.1 (OB2)
/CANH_1: C59.1, IC3.7 (CANH), J4.1, J5.1, R52.2
/CANL_1: C60.2, IC3.6 (CANL), J4.2, J5.2, R55.1
/DIR: U1.17 (PA7), U5.19 (DIR)
/DIR_ENC: IC2.8 (DIR), R12.2, U1.3 (PC14)
/INT1: U7.4 (INT1)
/INT2: U7.9 (INT2)
/OUT: IC2.3 (OUT), U1.10 (PA0)
/RXD_1: IC3.4 (RXD), U1.45 (PB8)
/SCL: IC2.7 (SCL), R56.1, U1.42 (PB6), U7.13 (SCL)
/SDA: IC2.6 (SDA), R57.1, U1.43 (PB7), U7.14 (SDA)
/STBY_1: IC3.8 (STB), R10.2, U1.29 (PA8)
/STDBY_DRV: U1.16 (PA6), U5.20 (STDBY)
/STEP: U1.19 (PB1), U5.16 (STEP)
/SWCLK/TCK: J1.4 (SWCLK/TCK), J3.4, U1.37 (PA14)
/SWDIO/TMS: J1.2 (SWDIO/TMS), J3.2, U1.34 (PA13)
/SWO/TDO: J1.6 (SWO/TDO), J3.6, U1.39 (PB3)
/TXD_1: IC3.1 (TXD), U1.46 (PB9)
/USB+: J6.A6 (D+), J6.B6 (D+), R11.1, U1.33 (PA12)
/USB-: J6.A7 (D-), J6.B7 (D-), U1.32 (PA11)
/~EN_DRV: R58.1, U1.22 (PB11), U5.2 (~EN)
/~PD/UART: U1.30 (PA9), U5.14 (~PD/UART)
/~RESET: C1.2, J1.10 (~RESET), J3.10, R1.2, SW1.1 (A), U1.7 (NRST)
GND: C1.1, C2.1, C10.1, C20.1, C24.2, C25.2, C26.1, C27.1, C28.1, C29.1, C31.1, C39.1, C40.1, C59.2, C60.1, H5.1 (1_1), H6.1 (1_1), H7.1 (1_1), H8.1 (1_1), IC2.4 (GND), IC3.2 (GND), IC3.9 (EP), J1.3 (GND), J1.5 (GND), J1.9 (GNDDetect), J3.3, J3.9, J4.3, J5.3, J6.A1 (GND), J6.A8 (SBU1), J6.A12 (GND), J6.B1 (GND), J6.B8 (SBU2), J6.B12 (GND), J6.SH (SHIELD), JP1.1 (A), JP2.1 (A), JP5.1 (A), JP6.1 (A), R2.1, R4.2, R5.2, R6.2, R7.2, SW1.2 (B), U1.8 (VSSA), U1.23 (VSS), U1.35 (VSS), U1.47 (VSS), U5.3 (GND), U5.7 (SPREAD), U5.9 (MS1/AD0), U5.10 (MS2/AD1), U5.11 (DIAG), U5.12 (INDEX), U5.13 (CLK), U5.18 (GND), U5.25 (NC), U5.29 (GND), U7.1 (SDO/SA0), U7.2 (SDX), U7.3 (SCX), U7.6 (GND), U7.7 (GND); also elsewhere on the board
unnamed: D5.2, J6.A4 (VBUS), J6.A9 (VBUS), J6.B4 (VBUS), J6.B9 (VBUS)
unnamed: IC2.5 (PGO), JP2.2 (B)
unnamed: J6.A5 (CC1), R6.1
unnamed: J6.B5 (CC2), R7.1
unnamed: JP1.2 (B), U1.26 (PB13)
unnamed: D5.1, JP3.1 (A)
unnamed: JP4.1 (A), R55.2
unnamed: JP4.2 (B), R52.1
unnamed: JP5.2 (B), U1.27 (PB14)
unnamed: JP6.2 (B), U1.28 (PB15)
unnamed: R2.2, U1.44 (BOOT0)
unnamed: C2.2, U1.5 (PD0), ye1.2
unnamed: C29.2, U1.6 (PD1), ye1.1
unnamed: C31.2, U5.8 (5VOUT)
unnamed: R5.1, U5.23 (BRA)
unnamed: R4.1, U5.27 (BRB)
unnamed: C22.1, U5.5 (CPI)
unnamed: C22.2, U5.4 (CPO)
unnamed: C30.1, U5.6 (VCP)

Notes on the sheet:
Power
Connector
VMEAS
Absolute encoder
CAN
USB
Mounting
